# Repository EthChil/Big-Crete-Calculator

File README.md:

# Big-Crete-Calculator
Hardware and Software for the Big Crete Calculator

Further documentation can be found in the documentation section. The goal of this project is to build a competent calculator based on the Artix-7 A200T which I can use for future FPGA projects.

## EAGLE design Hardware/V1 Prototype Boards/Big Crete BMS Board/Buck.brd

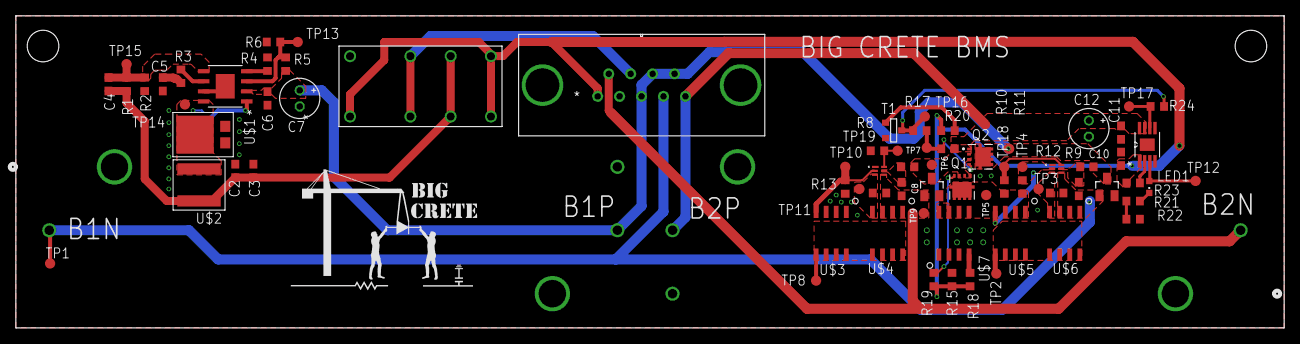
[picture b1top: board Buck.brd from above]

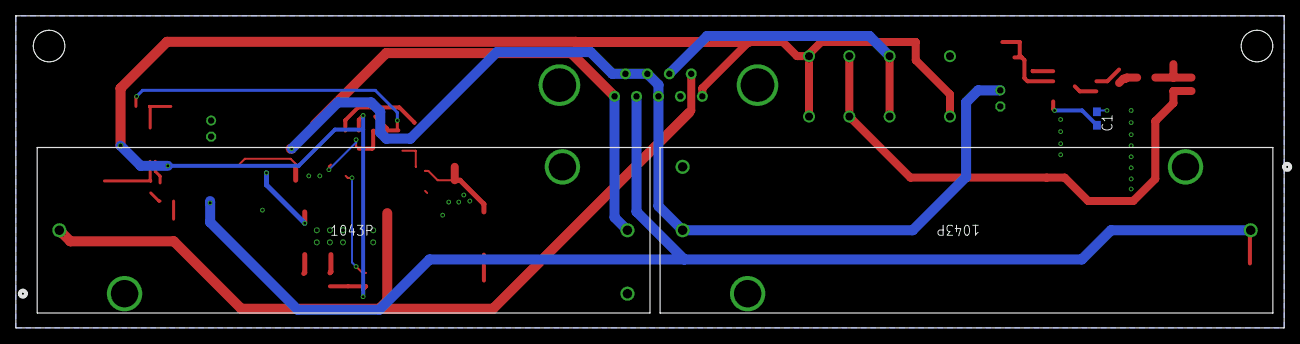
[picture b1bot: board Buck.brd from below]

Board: 2 copper layers, 160.0 x 39.4 mm, 76 parts (3 on the bottom side), 36 nets.

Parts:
C1, C8, C9, C10, C11: 0.1uF; C0603
C2, C3: 22uF; C0603
C4: 220pF; C0603
C5: 0.01uF; C0603
C6: 4.7uF; C0603
C7, C12: 47uF; E2-5
D1, D2: SOT23
J1, J2: 1043P; CONN2_1043P_KEY
J3: L77TSEH09SOL2; CONN_L77TSEH09SOL2_AMP
LED1: CHIPLED_0603
Q1, Q2: AONR21321; TRANS_AONR21321
R1: 52.3k; R0603
R2, R6, R15, R16: 10k; R0603
R3: 12.7k; R0603
R4: 174k; R0603
R5: 45k; R0603
R7, R9: 330; R0603
R8, R10: 2.2k; R0603
R11, R12, R13, R14: 5M; R0603
R17, R18, R19, R20, R21, R22, R24: 100; R0603
R23: 10; R0603
T1: SOT-23
TP1, TP2, TP3, TP4, TP5, TP6, TP7, TP8, TP9, TP10, TP11, TP12, TP13, TP14, TP15, TP16, TP17, TP18, TP19: TPTP13R; TP13R
U1: TPS54540DDA; DDA8_3P1X2P4_TEX
U2, U3: BQ29732DSER; DSE6_TEX
U4: BQ24202DGN; DGN8_1P57X1P89
U5: J104D2C5VDC.20S; RELAY8_J104D2C5VDC.20S_CRS
U$1: SS3P5LHM3_A/H; TO-227A
U$2: XAL6060-223MEC; XAL6060
U$3, U$4, U$5, U$6, U$7: DMG4496SSS; SO-8

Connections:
B1N: C9.2, D1.1, J1.4, J3.4, R12.2, TP1.TP, U3.4, U$6.1, U$6.2, U$6.3
B1P: C6.1, C7.+, D1.3, J1.2, J3.3, J3.8, J3.9, Q2.5, Q2.6, Q2.7, Q2.8, Q2.9, Q2.9_1, Q2.9_2, R5.2, R9.1, U1.2
B2N: C8.2, D2.1, J2.4, J3.6, R14.2, TP9.TP, U2.4, U$4.1, U$4.2, U$4.3
B2P: C11.2, C12.+, D2.3, J2.2, J3.5, Q1.1, Q1.2, Q1.3, Q2.1, Q2.2, Q2.3, R7.1, R16.2, TP6.TP, U4.7, U4.8
CHARGE: C10.1, J3.1, R15.1, R18.2, R19.1, R20.2, R23.2, U4.1, U5.1, U5.4, U5.5
FPGA_OUT: J3.7, U5.2, U5.7
GND: C2.2, C3.2, C5.2, C6.2, C7.-, C10.2, C11.1, C12.-, J3.2, R2.1, R4.1, R6.1, R8.2, R13.1, R15.2, R22.2, T1.2, U1.7, U1.EPAD, U4.4, U4.9, U5.8, U$1.A$1, U$1.A$2, U$3.1, U$3.2, U$3.3, U$7.1, U$7.2, U$7.3
unnamed: C1.2, U1.1
unnamed: C1.1, TP14.TP, U1.8, U$1.K, U$2.1
unnamed: C2.1, C3.1, C4.1, R1.2, U5.3, U5.6, U$2.2
unnamed: C5.1, R3.1
unnamed: C4.2, R1.1, R2.2, TP15.TP, U1.5
unnamed: R3.2, U1.6
unnamed: Q2.4, R16.1, R17.2, TP7.TP
unnamed: R4.2, U1.4
unnamed: R5.1, R6.2, TP13.TP, U1.3
unnamed: TP8.TP, U$3.5, U$3.6, U$3.7, U$3.8, U$4.5, U$4.6, U$4.7, U$4.8
unnamed: R13.2, TP10.TP, U2.2, U$3.4
unnamed: R14.1, TP11.TP, U2.3, U$4.4
unnamed: C8.1, R7.2, U2.5
unnamed: TP2.TP, U$5.5, U$5.6, U$5.7, U$5.8, U$6.5, U$6.6, U$6.7, U$6.8
unnamed: R8.1, TP19.TP, U2.6
unnamed: R11.2, TP4.TP, U3.2, U$5.4
unnamed: R24.2, TP17.TP, U4.6
unnamed: R12.1, TP3.TP, U3.3, U$6.4
unnamed: C9.1, R9.2, U3.5
unnamed: R10.1, TP18.TP, U3.6
unnamed: R18.1, U$7.4
unnamed: Q1.4, R19.2
unnamed: Q1.5, Q1.6, Q1.7, Q1.8, Q1.9, Q1.9_1, Q1.9_2, R10.2, R11.1, TP5.TP, U$5.1, U$5.2, U$5.3, U$7.5, U$7.6, U$7.7, U$7.8
unnamed: R20.1, T1.3
unnamed: LED1.C, R21.1
unnamed: R21.2, R22.1
unnamed: LED1.A, TP12.TP, U4.3
unnamed: R23.1, U4.2
~CHARGE: R17.1, R24.1, T1.1, TP16.TP

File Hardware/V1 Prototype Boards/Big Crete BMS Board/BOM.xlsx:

Index | Quantity | Designator | Part Number | Manufacturer Part Number | Description | Customer Reference | Backorder | Unit Price | Extended Price | Ordered | Soldered
1 | 3 |  | SS3P5LHM3_A/HGICT-ND | SS3P5LHM3_A/H | DIODE SCHOTTKY 50V 3A TO277A |  | 0 | 0.63 | $1.89
2 | 10 | C2,C3 | 490-13243-1-ND | GRM187R61A226ME15D | CAP CER 22UF 10V X5R 0603 |  | 0 | 0.29199999999999998 | $2.92 | y | n
3 | 10 | C4 | 732-7974-1-ND | 885012206055 | CAP CER 220PF 25V X7R 0603 |  | 0 | 2.1999999999999999E-2 | $0.22 | y | n
4 | 10 |  | 732-8007-1-ND | 885012206089 | CAP CER 10000PF 50V X7R 0603 |  | 0 | 1.9E-2 | $0.19
5 | 10 | C11, C10, C8, C9 | 1276-1935-1-ND | CL10B104KB8NNWC | CAP CER 0.1UF 50V X7R 0603 |  | 0 | 0.02 | $0.20 | y | n
6 | 10 | C7, C12 | 732-8823-1-ND | 860020472006 | CAP ALUM 47UF 20% 25V RADIAL |  | 0 | 0.1 | $1.00 | y | n
7 | 4 | U2, U3 | 296-44132-1-ND | BQ29732DSET | IC BATT PROT LI-ION 1CELL 6WSON |  | 0 | 1.25 | $5.00 | n | y
8 | 10 | U$4, U$3, U$6, U$5, U$7 | DMG4496SSS-13DICT-ND | DMG4496SSS-13 | MOSFET N-CH 30V 10A 8SOP |  | 0 | 0.39100000000000001 | $3.91 | n | y
9 | 3 | Q2, Q1 | 785-1797-1-ND | AONR21321 | MOSFET P-CH 30V 24A 8DFN |  | 0 | 0.48 | $1.44 | n | y
10 | 10 | D2, D1 | MMBZ5230BLT1GOSCT-ND | MMBZ5230BLT1G | DIODE ZENER 4.7V 225MW SOT23-3 |  | 0 | 0.13800000000000001 | $1.38 | n | y
11 | 10 | T1 | RUC002N05HZGT116CT-ND | RUC002N05HZGT116 | MOSFET N-CH 50V 200MA SST3 |  | 0 | 0.17699999999999999 | $1.77 | n | y
12 | 2 | U4 | 296-12411-5-ND | BQ24202DGN | IC BATT CHG LI-ION 1CELL 8MSOP |  | 0 | 6.18 | $12.36 | n | y
13 | 10 | LED1 | 3147-B1931NB--20C006714U1930CT-ND | B1931NB--20C006714U1930 | LED BLUE CLEAR 1608 SMD |  | 0 | 5.1999999999999998E-2 | $0.52 | n | y
14 | 3 | J2, J1 | 36-1043P-ND | 1043P | BATT HOLDER 18650 1 CELL PC PIN |  | 0 | 3.11 | $9.33 | n | n
15 | 5 | U5 | 2449-J104D2C5VDC.20S-ND | J104D2C5VDC.20S | RELAY UL GEN PURP DPDT 2C 5VDC |  | 0 | 1.21 | $6.05 | y | n
16 | 5 | J3 | L77TSEH09SOL2-ND | L77TSEH09SOL2 | CONN D-SUB RCPT 9POS VERT SLDR |  | 0 | 1.34 | $6.70 | n | n
17 | 1 |  | ARF2492-ND | 034-1018-12G | CONN HDBNC JCK STR 75OHM EDGEMNT |  | 0 | 10.4 | $10.40
 |  |  |  |  |  |  |  | Subtotal | $65.28
18 | 10 | C6 |  |  | CAP CER 4.7uF 0603 |  |  |  |  | y | n
19 | 20 | R24, R22, R21, R20, R17, R19, R18 |  |  | RES 100 Ohm 0603 |  |  |  |  | y | n
20 | 10 | R23 |  |  | RES 10 Ohm 0603 |  |  |  |  | y | n
22 | 10 | R16, R15 |  |  | RES 10k 0603 |  |  |  |  | y | n
23 | 10 | R7, R9 |  |  | RES 330 0603 |  |  |  |  | y | n
24 | 10 | R14, R13, R12, R11 |  |  | RES 5 Mohm 0603 |  |  |  |  | y | n
25 | 10 | R8, R10 |  |  | RES 2.2k 0603 |  |  |  |  | y | n

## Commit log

2021-02-07 created initial template file, this will hold common IP for things like RAM and pinouts
2021-02-07 added altium project and sodimm socket files
2021-02-26 Outlined basic altium structure
2021-02-27 Updated vivado
2021-02-27 Completed labeling DQ channels on FPGA
2021-02-27 routed dqs differentials
2021-02-27 Finished population ram NETs on FPGA
2021-02-27 Updated errors realized everything so far has been designed for ECC ddr3L
2021-02-27 Redid the FPGA ram connections and cleared the RAM
2021-02-28 Combined A200T schematics into one, this should make it easier to navigate
2021-02-28 Connected ram and FPGA, fixed the template RTL file
2021-02-28 Expanded design documentation
2021-03-02 updated footprints for spi
2021-03-02 updated the readme and took the repo public
2021-05-02 First commit from new pc
2021-05-04 Updated design journal
2021-05-12 restructured hardware and finished layout on switch breakout
2021-05-12 updated the board fixed silkscreens and stuff ready to order now
2021-06-06 re architechted project structure
2021-08-04 mods to vivado swapped chip
2021-08-05 Touched up vivado added some display signals
2021-09-13 Latest edits
2022-01-03 calculator work
2022-02-28 added to documentation, doing architecture for calculator
2022-05-18 added big crete bms dev board
2022-08-18 Latest updates to design
2022-08-18 reorganized files and tested switch board
2022-08-19 Cleaned up files further
2022-08-19 updated docs
2022-08-19 updated arduino test code and docs
2022-09-04 made mockups of design
2022-09-05 updated design further
2022-09-05 updated full assem
2022-09-12 updates to design with backplate design files
2023-01-07 display running
2023-01-08 added two new test pcbs for 2p configuration (boost and charger)
2023-03-24 updated design
2023-04-04 fixed spacing on key switches
2023-04-05 Swapped inter board header and started laying out switchboard
2023-04-07 Switchboard laid out and cleaned
2023-04-07 cleaned solidworks model up and fixed board thickness on export
2023-04-07 dxfs made, front and backplates ordered
2023-04-07 updated mainboard to reflect changes required, routing not done yet
2023-04-07 honestly too tired to route the mainboard saving the state for now
2023-04-09 updated gitignore for mac
2023-04-09 remove DS_Store
2023-04-11 cleaned up project logs
2023-04-12 polished off mainboard and integrated into mechanical
2023-04-12 JLCPCB boards ordered
2023-04-19 documentation reorganization
2023-05-02 docs
2023-05-06 updated journal
2023-09-29 Schematic clean and updated, stackup fixed time to start laying the design out
2023-10-05 added a kicad project for testing
2023-10-10 updated what needs to be done
2023-10-10 worked on the digital design a bit
2023-10-27 Major revisions and progress towards V2.5
2023-10-28 mainboard laid out
2023-11-02 calculating
2023-11-15 Boards for V2.5 ready to be sent out
2024-01-30 sent out boards for Rev 2
2024-02-05 sim changes
2024-04-02 updated interposer
2024-04-07 updated STL for interposer to give more mainboard clearance

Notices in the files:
parts and their libraries:
COPYRIGHT: Copyright (C) 2022 Ultra Librarian. All rights reserved.
